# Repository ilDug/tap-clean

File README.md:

# tap-clean
Progetto arduino per la miscelazione dei detersivi.

## Funzionamento

Quattro pompe dosano il detersivo,  l'ammorbidente,  l'anticalcare e l'igenizzante in una tazza pronta per essere versata nel vassoio della lavatrice.

### Led

- PWR: apparecchio acceso
- DETERSIVO:  (lampeggia quando la pompa è attiva)
- ANTICALCARE: (lampeggia quando la pompa è attiva)
- IGENIZZANTE: (lampeggia quando la pompa è attiva)
- AMMORBIDENTE: (lampeggia quando la pompa è attiva)
- LEVEL: 3 led che indicano il livello di dosaggio

Otto led in totale che posso comandare con uno SHIFT_REGISTER.

### Programmi

Alla pressione del pulsante *PRG*  posso navigare tra i programmi. Ad un programma corrispondono una serie di led accesi che evidenziano quali sostanze saranno pompate .

| #            | P1 | P2 | P3 | CLN |
|--------------|----|----|----|-----|
| DETERSIVO    | X  |    | X  | X   |
| ANTICALCARE  | X  |    | X  | X   |
| IGENIZZANTE  | X  |    |    | X   |
| AMMORBIDENTE |    | X  |    | X   |

Alla pressione del pulsante *LVL* si possono selezionare tre livelli di dosaggio.A partire dal dosaggio medio, ogni pressione ciclicamente aumenta o diminuisce il livello.

Alla pressioen del pulsante *RUN* avvia il programma di miscelazione e attiva le pompe.

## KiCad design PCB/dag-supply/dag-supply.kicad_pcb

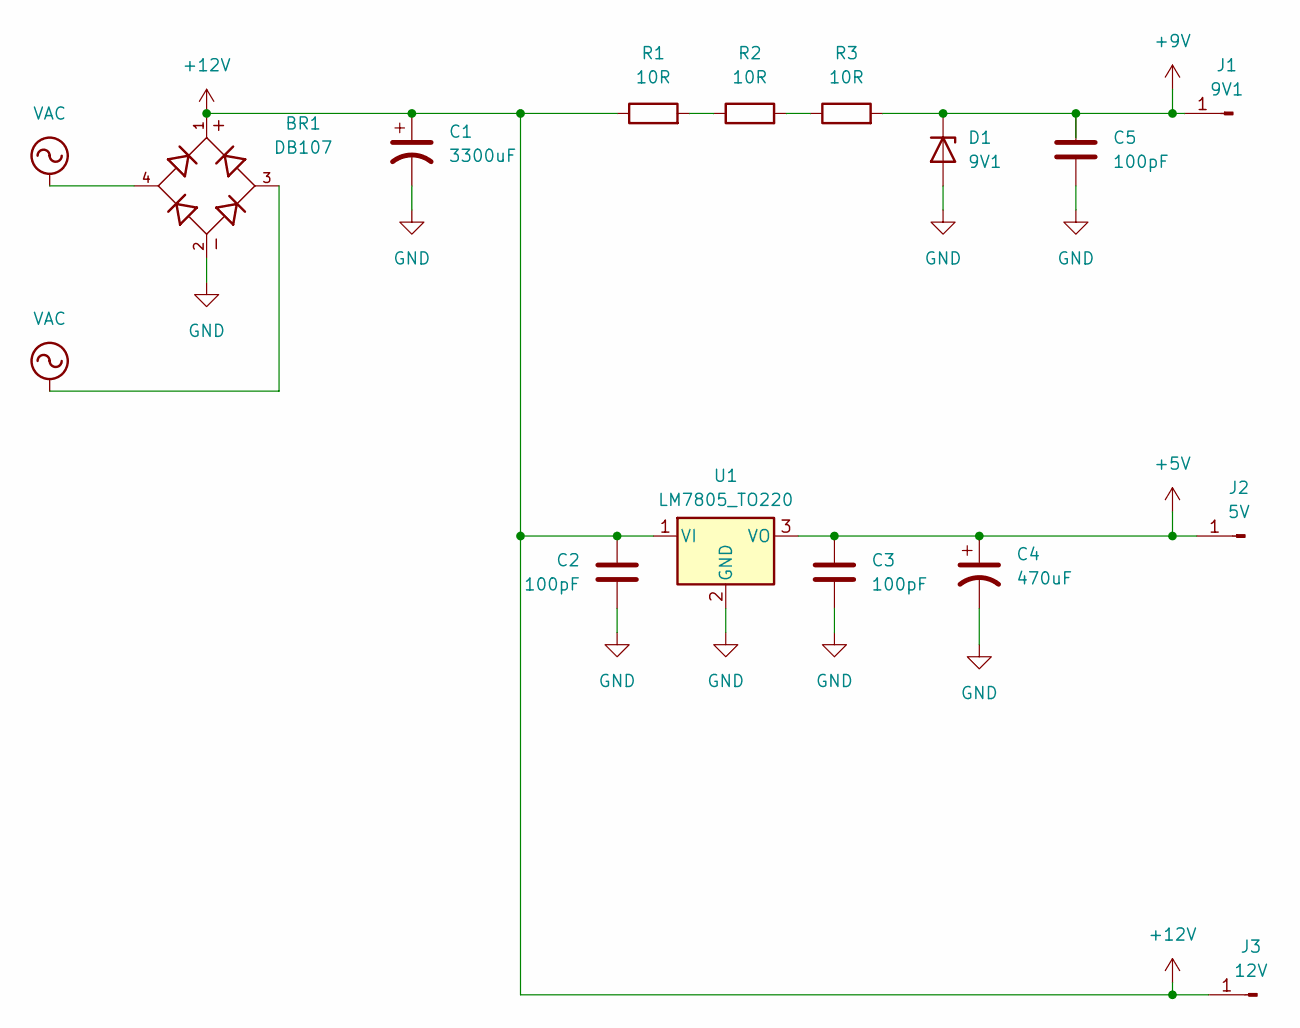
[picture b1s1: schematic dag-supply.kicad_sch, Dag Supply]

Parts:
BR1: DB107; DIP825W50P509L880H320Q4; PARTREV 13
C1: 3300uF; CP_Radial_D12.5mm_P5.00mm
C2, C3, C5: 100pF; C_Disc_D4.3mm_W1.9mm_P5.00mm
C4: 470uF; CP_Radial_D8.0mm_P2.50mm
D1: 9V1; D_T-1_P10.16mm_Horizontal
J1: 9V1; PinHeader_1x01_P1.00mm_Vertical
J2: 5V; PinHeader_1x01_P1.00mm_Vertical
J3: 12V; PinHeader_1x01_P1.00mm_Vertical
R1, R2, R3: 10R; R_Axial_DIN0309_L9.0mm_D3.2mm_P15.24mm_Horizontal
U1: LM7805_TO220; TO-220-3_Vertical

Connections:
+5V: C3.1, C4.1, J2.1, U1.3 (VO)
+9V: C5.1, D1.1 (K), J1.1, R3.2
+12V: BR1.1, C1.1, C2.1, J3.1, R1.1, U1.1 (VI)
GND: BR1.2, C1.2, C2.2, C3.2, C4.2, C5.2, D1.2 (A), U1.2 (GND)
unnamed: R1.2, R2.1
unnamed: R2.2, R3.1
VAC: BR1.3, BR1.4

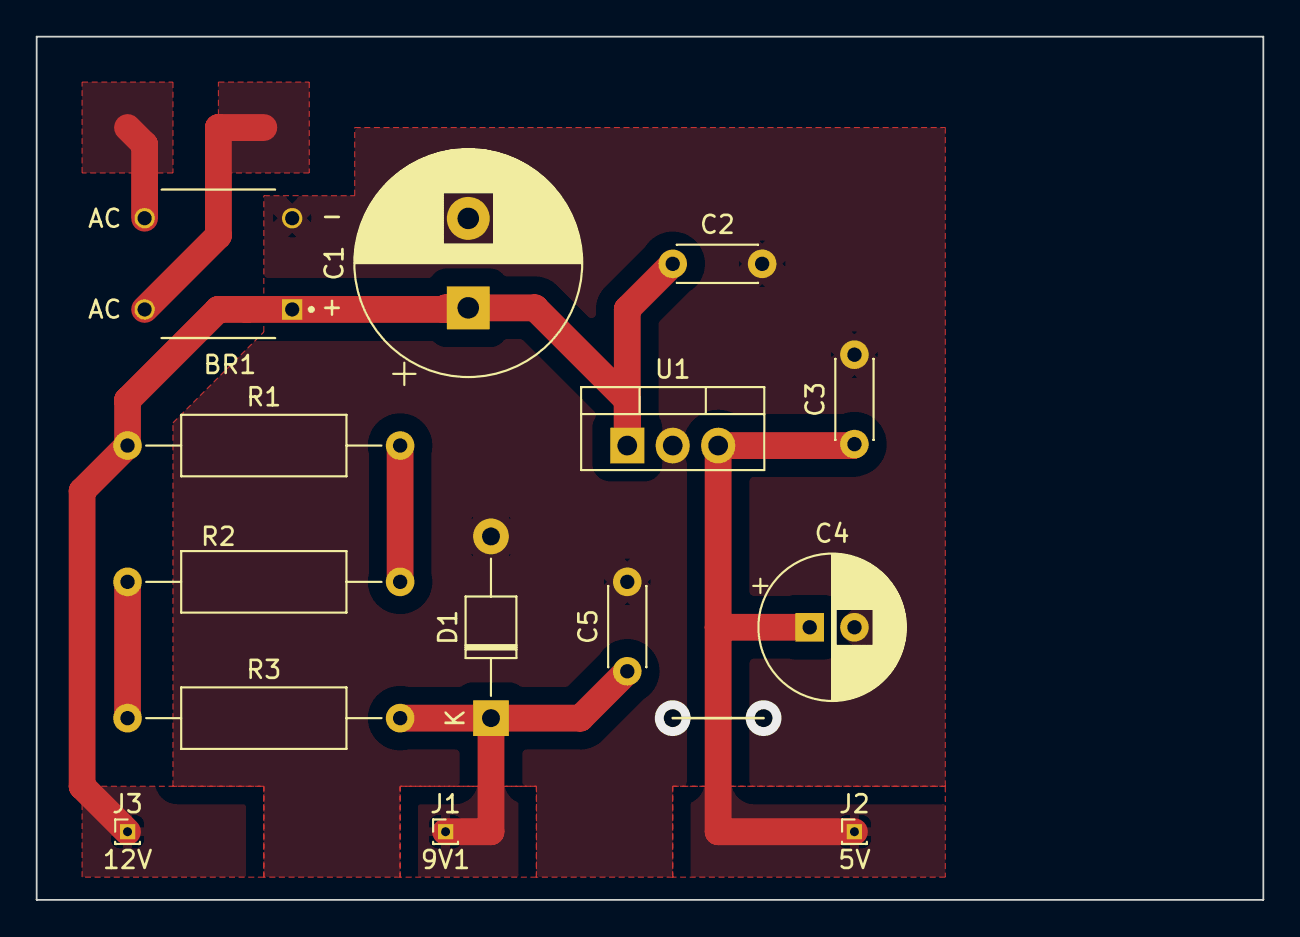
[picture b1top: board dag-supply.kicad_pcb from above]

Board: 2 copper layers, 68.6 x 48.3 mm, 14 parts (0 on the bottom side), 7 nets.

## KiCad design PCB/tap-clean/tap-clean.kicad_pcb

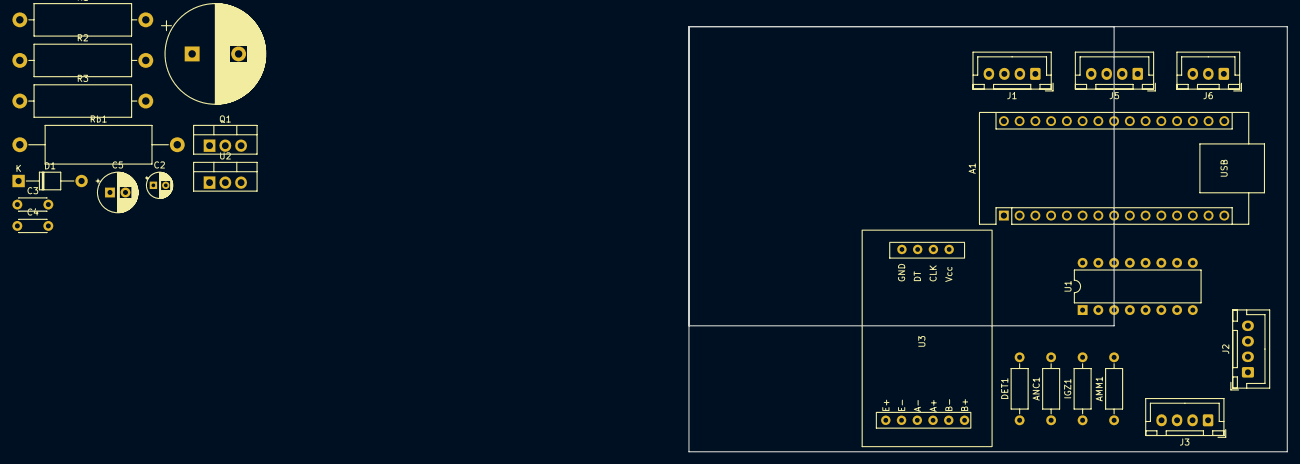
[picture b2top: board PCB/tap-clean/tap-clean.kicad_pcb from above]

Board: 2 copper layers, 96.5 x 68.6 mm, 24 parts (0 on the bottom side), 29 nets, no tracks yet.

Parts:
A1: Arduino_Nano_v3.x; Arduino_Nano
AMM1: 330R; R_Axial_DIN0207_L6.3mm_D2.5mm_P10.16mm_Horizontal
ANC1: 330R; R_Axial_DIN0207_L6.3mm_D2.5mm_P10.16mm_Horizontal
C1: 1000uF; CP_Radial_D16.0mm_P7.50mm
C2: 330pF; CP_Radial_D4.0mm_P2.00mm
C3, C4: 100pF; C_Disc_D4.3mm_W1.9mm_P5.00mm
C5: 470uF; CP_Radial_D6.3mm_P2.50mm
D1: 9V1; D_T-1_P10.16mm_Horizontal
DET1: 330R; R_Axial_DIN0207_L6.3mm_D2.5mm_P10.16mm_Horizontal
IGZ1: 330R; R_Axial_DIN0207_L6.3mm_D2.5mm_P10.16mm_Horizontal
J1: Stepper1; JST_XH_B4B-XH-A_1x04_P2.50mm_Vertical
J2: Relay; JST_XH_B4B-XH-A_1x04_P2.50mm_Vertical
J3: Led; JST_XH_B4B-XH-A_1x04_P2.50mm_Vertical
J5: LCD; JST_XH_B4B-XH-A_1x04_P2.50mm_Vertical
J6: CTRL; JST_XH_B3B-XH-A_1x03_P2.50mm_Vertical
Q1: TIP42; TO-220-3_Vertical
R1, R3: 10R; R_Axial_DIN0516_L15.5mm_D5.0mm_P20.32mm_Horizontal
R2: 5R; R_Axial_DIN0516_L15.5mm_D5.0mm_P20.32mm_Horizontal
Rb1: 1.5R; R_Axial_DIN0617_L17.0mm_D6.0mm_P25.40mm_Horizontal
U1: 74HC595; DIP-16_W7.62mm
U2: LM7805_TO220; TO-220-3_Vertical
U3: HX711

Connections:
+5V: C4.1, C5.1, J5.1, Q1.2 (C), U1.10 (~SRCLR), U1.16 (VCC), U2.3 (VO), U3.4 (Vcc)
+9V: A1.30 (VIN), C3.1, D1.1 (K), R3.2
+12V: C1.1, Q1.3 (E), R1.1, Rb1.1
GND: A1.4 (GND), A1.29 (GND), C1.2, C2.2, C3.2, C4.2, C5.2, D1.2 (A), J5.4, U1.8 (GND), U1.13 (~OE), U2.2 (GND), U3.1 (GND)
unnamed: A1.20 (A1), J6.1
unnamed: A1.21 (A2), J6.2
unnamed: A1.22 (A3), J6.3
unnamed: A1.23 (A4), J5.2
unnamed: A1.24 (A5), J5.3
unnamed: A1.5 (D2), U1.14 (SER)
unnamed: A1.6 (D3), U1.11 (SRCLK)
unnamed: A1.7 (D4), U1.12 (RCLK)
unnamed: A1.11 (D8), U3.2 (DT)
unnamed: A1.12 (D9), U3.3 (CLK)
unnamed: J2.1, U1.4 (QE)
unnamed: J2.2, U1.5 (QF)
unnamed: J2.3, U1.6 (QG)
unnamed: J2.4, U1.7 (QH)
unnamed: DET1.1, J3.1
unnamed: ANC1.1, J3.2
unnamed: IGZ1.1, J3.3
unnamed: AMM1.1, J3.4
unnamed: C2.1, Q1.1 (B), Rb1.2, U2.1 (VI)
unnamed: R1.2, R2.1
unnamed: R2.2, R3.1
unnamed: DET1.2, U1.15 (QA)
unnamed: ANC1.2, U1.1 (QB)
unnamed: IGZ1.2, U1.2 (QC)
unnamed: AMM1.2, U1.3 (QD)

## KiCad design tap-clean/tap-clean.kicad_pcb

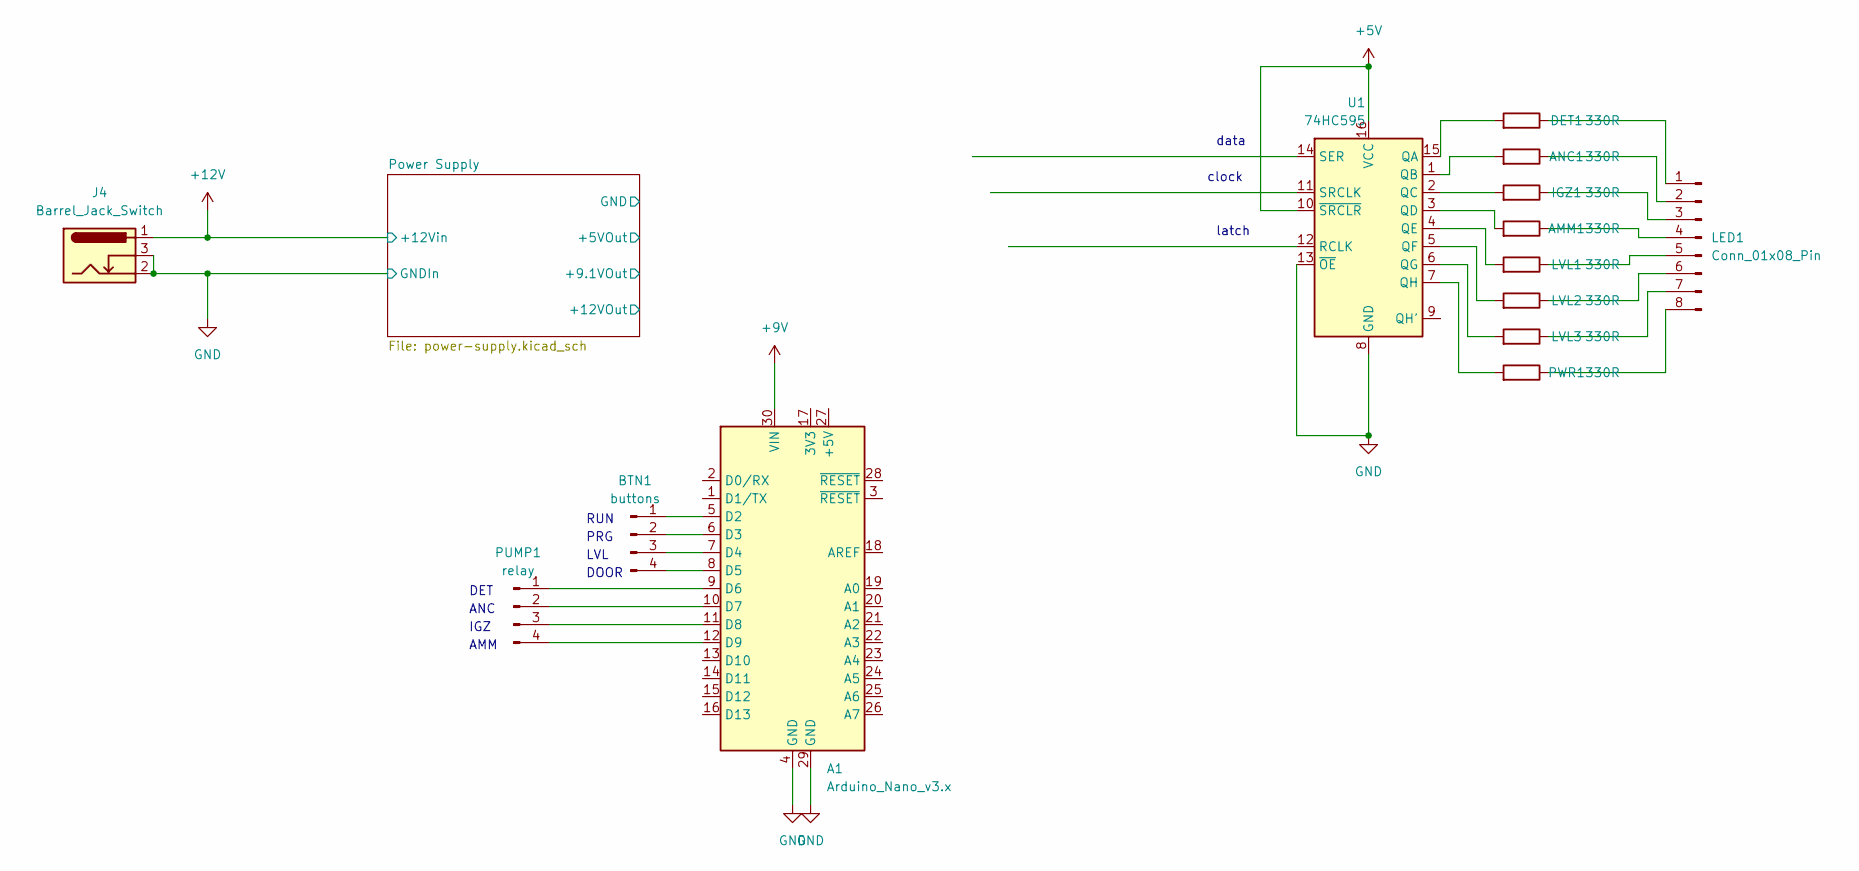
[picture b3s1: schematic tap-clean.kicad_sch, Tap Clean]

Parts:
A1: Arduino_Nano_v3.x; Arduino_Nano
AMM1: 330R; R_Axial_DIN0207_L6.3mm_D2.5mm_P10.16mm_Horizontal
ANC1: 330R; R_Axial_DIN0207_L6.3mm_D2.5mm_P10.16mm_Horizontal
BTN1: buttons; PinHeader_1x04_P2.54mm_Vertical
DET1: 330R; R_Axial_DIN0207_L6.3mm_D2.5mm_P10.16mm_Horizontal
IGZ1: 330R; R_Axial_DIN0207_L6.3mm_D2.5mm_P10.16mm_Horizontal
J4: Barrel_Jack_Switch
LED1: Conn_01x08_Pin; PinHeader_1x08_P2.54mm_Vertical
LVL1, LVL2, LVL3: 330R; R_Axial_DIN0207_L6.3mm_D2.5mm_P10.16mm_Horizontal
PUMP1: relay; PinHeader_1x04_P2.54mm_Vertical
PWR1: 330R; R_Axial_DIN0207_L6.3mm_D2.5mm_P10.16mm_Horizontal
U1: 74HC595; DIP-16_W7.62mm

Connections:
+5V: U1.10 (~SRCLR), U1.16 (VCC); also elsewhere on the board
+9V: A1.30 (VIN); also elsewhere on the board
GND: A1.4 (GND), A1.29 (GND), J4.2, J4.3, U1.8 (GND), U1.13 (~OE); also elsewhere on the board
unnamed: A1.23 (A4), U1.14 (SER)
unnamed: A1.24 (A5), U1.11 (SRCLK)
unnamed: A1.25 (A6), U1.12 (RCLK)
unnamed: A1.5 (D2), BTN1.1
unnamed: A1.6 (D3), BTN1.2
unnamed: A1.7 (D4), BTN1.3
unnamed: A1.8 (D5), BTN1.4
unnamed: A1.9 (D6), PUMP1.1
unnamed: A1.10 (D7), PUMP1.2
unnamed: A1.11 (D8), PUMP1.3
unnamed: A1.12 (D9), PUMP1.4
unnamed: DET1.1, LED1.1
unnamed: ANC1.1, LED1.2
unnamed: IGZ1.1, LED1.3
unnamed: AMM1.1, LED1.4
unnamed: LED1.5, LVL1.1
unnamed: LED1.6, LVL2.1
unnamed: LED1.7, LVL3.1
unnamed: LED1.8, PWR1.1
unnamed: DET1.2, U1.15 (QA)
unnamed: ANC1.2, U1.1 (QB)
unnamed: IGZ1.2, U1.2 (QC)
unnamed: AMM1.2, U1.3 (QD)
unnamed: LVL1.2, U1.4 (QE)
unnamed: LVL2.2, U1.5 (QF)
unnamed: LVL3.2, U1.6 (QG)
unnamed: PWR1.2, U1.7 (QH)

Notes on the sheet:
IGZ
PRG
data
clock
AMM
latch
ANC
LVL
DET
RUN
DOOR

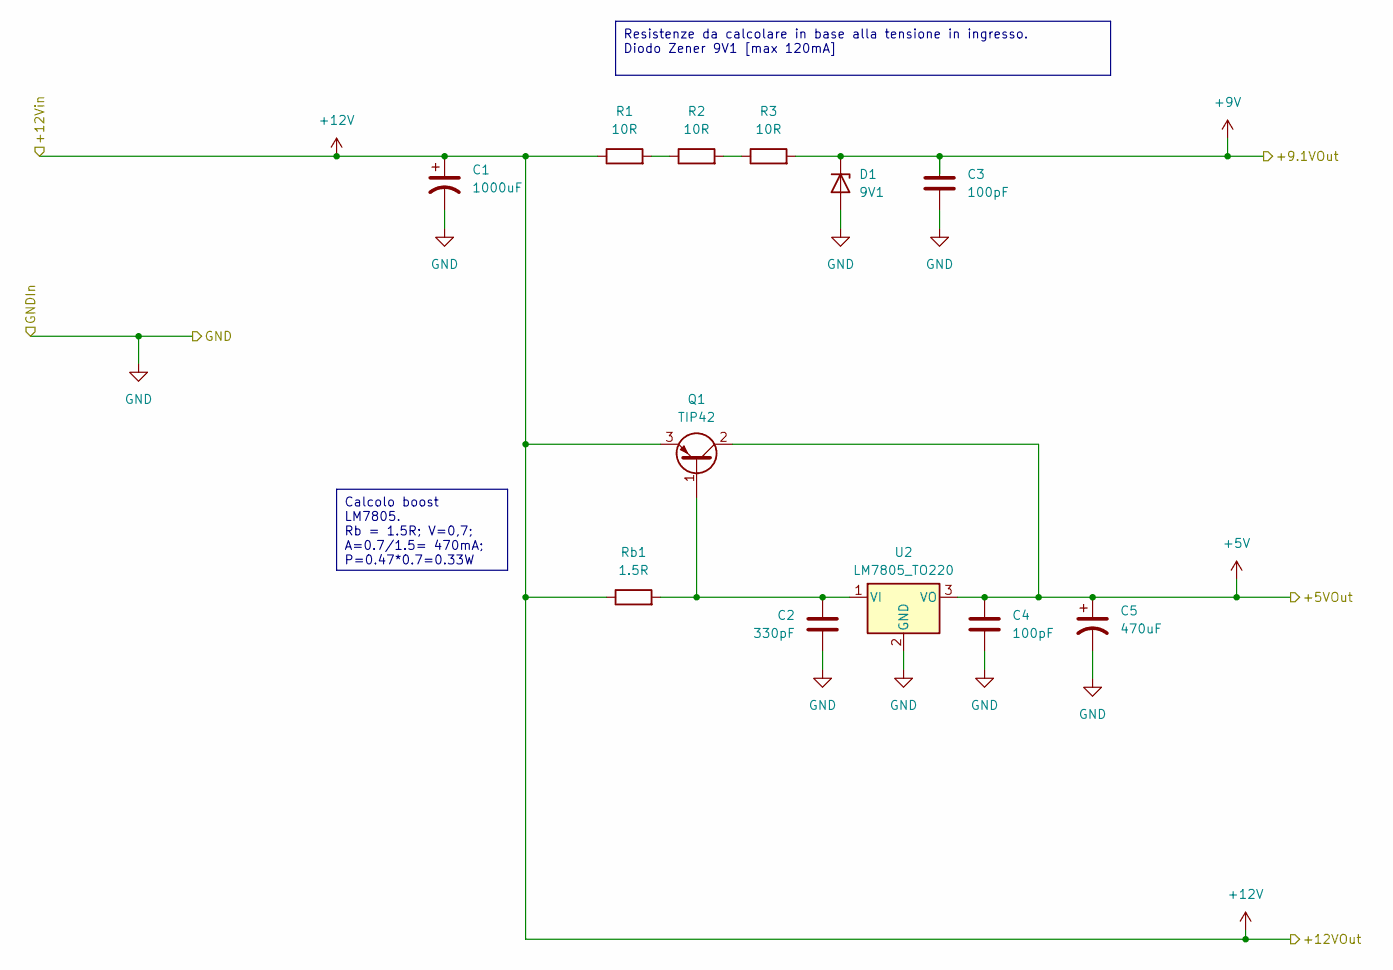
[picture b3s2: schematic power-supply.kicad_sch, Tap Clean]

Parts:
C1: 1000uF; CP_Radial_D16.0mm_P7.50mm
C2: 330pF; CP_Radial_D4.0mm_P2.00mm
C3, C4: 100pF; C_Disc_D4.3mm_W1.9mm_P5.00mm
C5: 470uF; CP_Radial_D6.3mm_P2.50mm
D1: 9V1; D_T-1_P10.16mm_Horizontal
Q1: TIP42; TO-220-3_Vertical
R1, R2, R3: 10R; R_Axial_DIN0516_L15.5mm_D5.0mm_P20.32mm_Horizontal
Rb1: 1.5R; R_Axial_DIN0617_L17.0mm_D6.0mm_P25.40mm_Horizontal
U2: LM7805_TO220; TO-220-3_Vertical

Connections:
+5V: C4.1, C5.1, Q1.2 (C), U2.3 (VO); also elsewhere on the board
+9V: C3.1, D1.1 (K), R3.2; also elsewhere on the board
+12V: C1.1, Q1.3 (E), R1.1, Rb1.1
GND: C1.2, C2.2, C3.2, C4.2, C5.2, D1.2 (A), U2.2 (GND); also elsewhere on the board
unnamed: C2.1, Q1.1 (B), Rb1.2, U2.1 (VI)
unnamed: R1.2, R2.1
unnamed: R2.2, R3.1

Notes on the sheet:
Resistenze da calcolare in base alla tensione in ingresso. Diodo Zener 9V1 [max 120mA]
Calcolo boost LM7805. Rb = 1.5R; V=0,7; A=0.7/1.5= 470mA; P=0.47*0.7=0.33W

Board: 2 copper layers, 25 parts (0 on the bottom side), 34 nets, no tracks yet.

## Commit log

2024-02-06 Istruzioni
2024-02-06 Add .DS_Store to .gitignore
2024-02-06 Adding dag timer
2024-02-06 adding utilities classes
2024-02-06 led contrller con i la somma degli stati
2024-02-07 iseparazione delle definizioni
2024-02-07 fixing
2024-02-07 working on main sketch
2024-02-07 adding stop program
2024-02-08 setting up dispenser class
2024-02-08 istanziato la classe dispenser nel loop
2024-02-08 removed unused files
2024-02-08 pcb dag-supply
2024-02-09 aggiunta la gestione della porta comandata da motorino stepper
2024-02-09 correto gli errori ella classe Door
2024-02-12 modificato il comportamento dela classe Dispenser
2024-02-12 working on pcb
2024-02-12 adding footprint to connections
2024-02-13 rebuld scaffolding
2024-02-13 suddiviso i due progetti in cartelle differenti
2024-02-13 compilata la logica di apertura. resta da vedere come fare a leggere la distanza con il sensore ultrasonico.
2024-02-13 eliminato PCB
2024-02-13 ennesimo refactoring
2024-02-13 puliza generale
2024-02-14 aggiunto bottone di toggle
2024-02-14 aggiunto sketch per il test dello stepper
2024-02-14 aggiutno la misura della distanza ultrasonica
2024-02-14 refactorin with display LCD
2024-02-15 formatting
2024-02-15 Add distance measurement logging in loop() function
2024-02-15 Add timeout for door closing
2024-02-15 update LCD initialization
2024-02-15 adding labels and completion to dispenser
2024-02-15 Update dispenser completion calculation
2024-02-15 add buzzer functionality
2024-02-15 Adding calibration test for scale
2024-02-16 Add LCD functionality to tap-clean.ino
2024-02-16 adding led when door is closed
2024-02-18 prigetto caricato (1)
2024-02-20 aggiunti i numri dei pins
2024-02-23 inserito la classe DagPot nello sketch
2024-02-23 Refactor DagPot class constructors and methods
2024-02-23 Refactor potentiometer initialization and usage
2024-02-23 potentiometer level from 0 to 15
2024-02-23 Add shift register functionality for controlling pumps
2024-02-23 same as prevouous
2024-03-09 primo test per la bilancia
2024-03-10 invertito le connessioni dei relay
2024-03-12 fixing last connection
2024-03-15 release candidate
